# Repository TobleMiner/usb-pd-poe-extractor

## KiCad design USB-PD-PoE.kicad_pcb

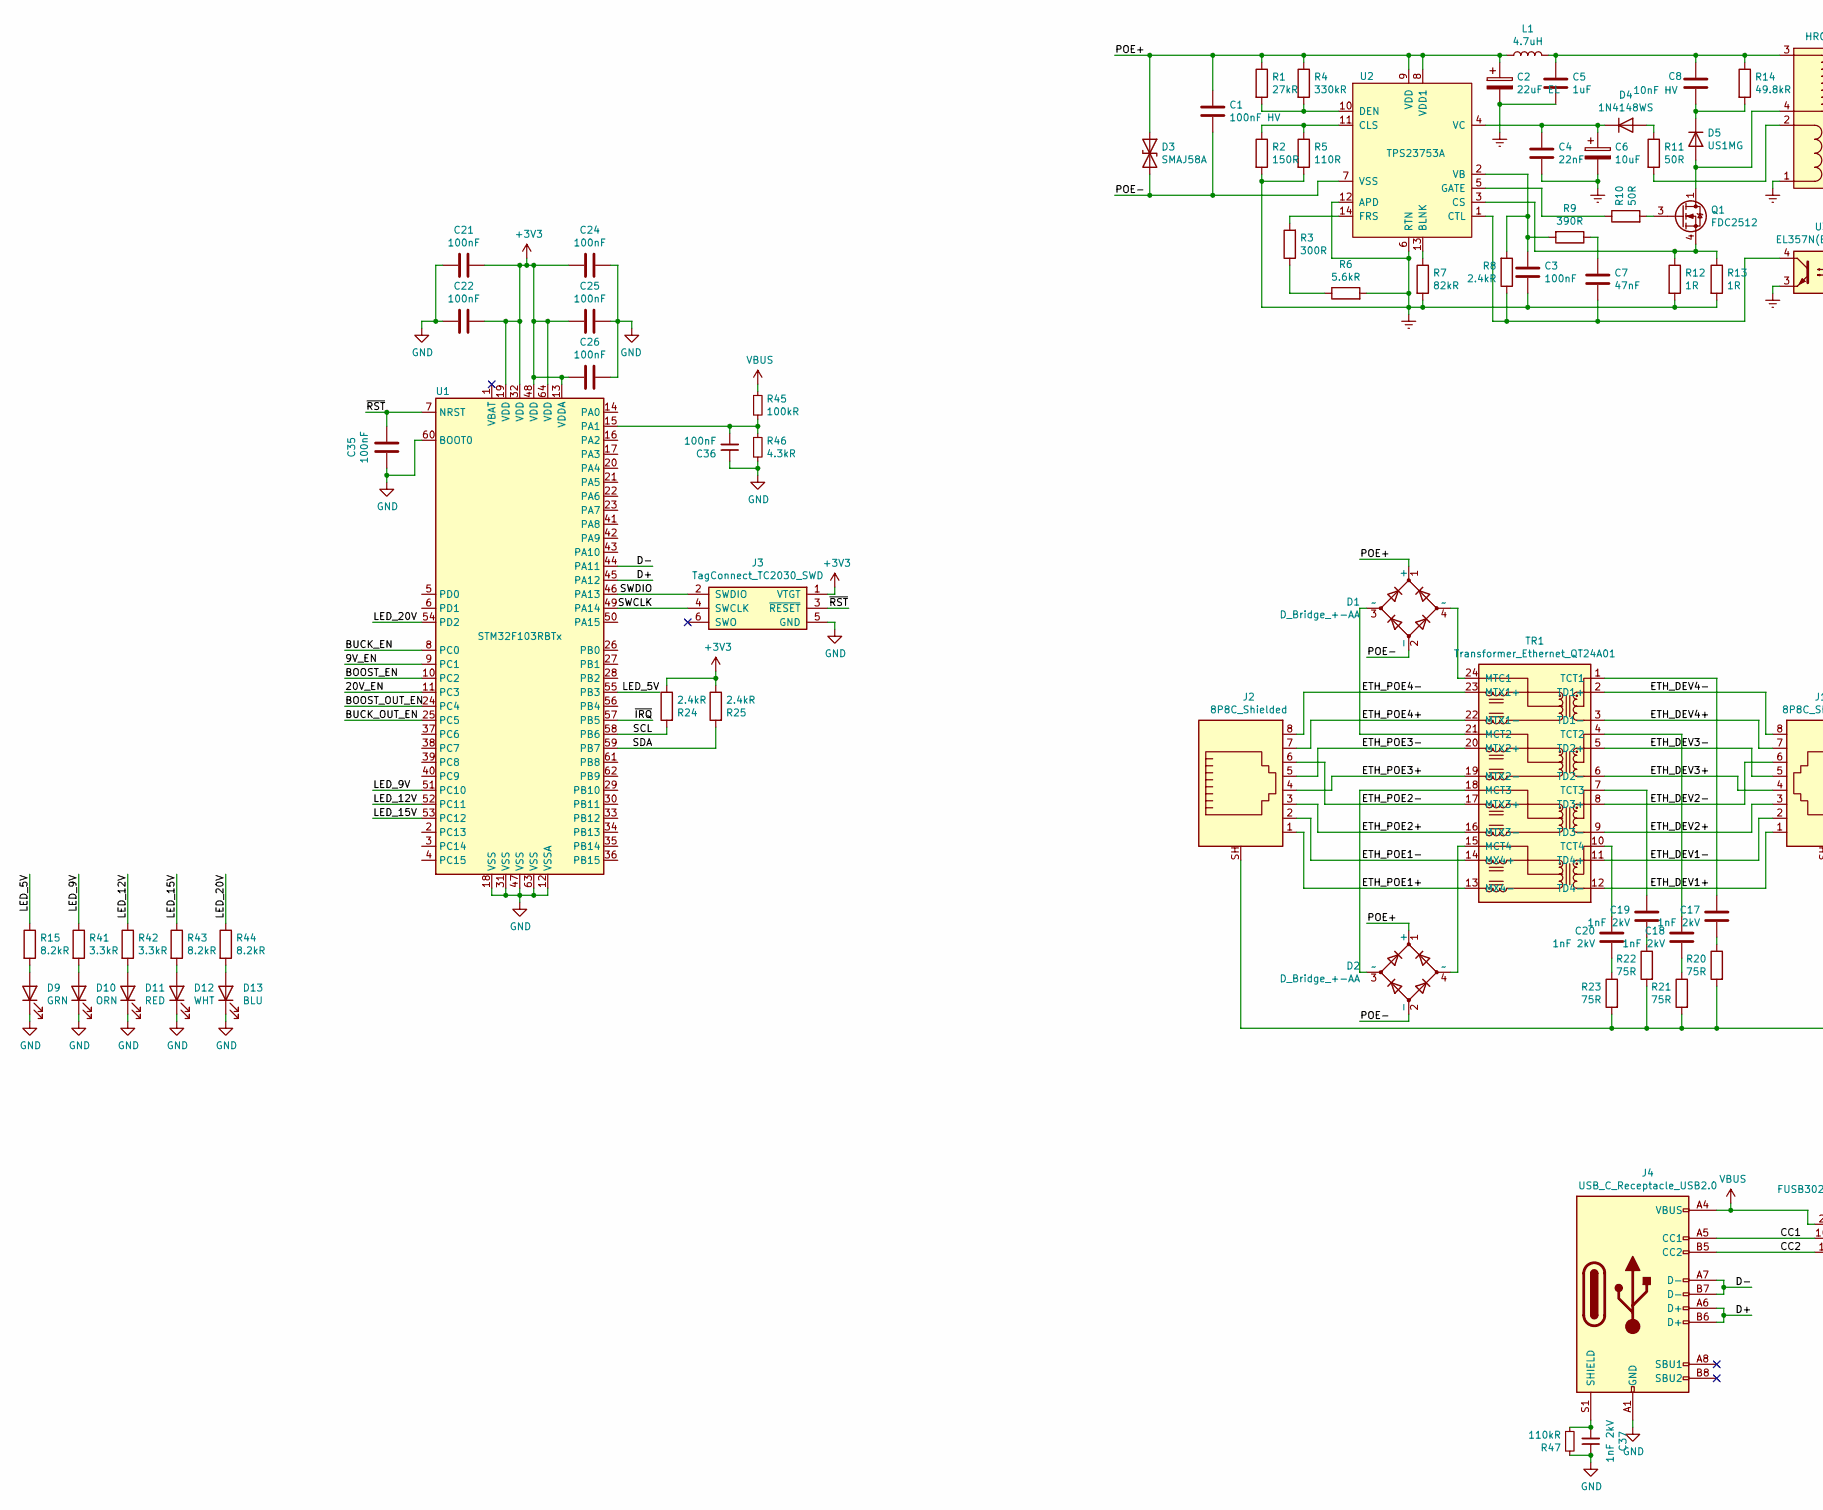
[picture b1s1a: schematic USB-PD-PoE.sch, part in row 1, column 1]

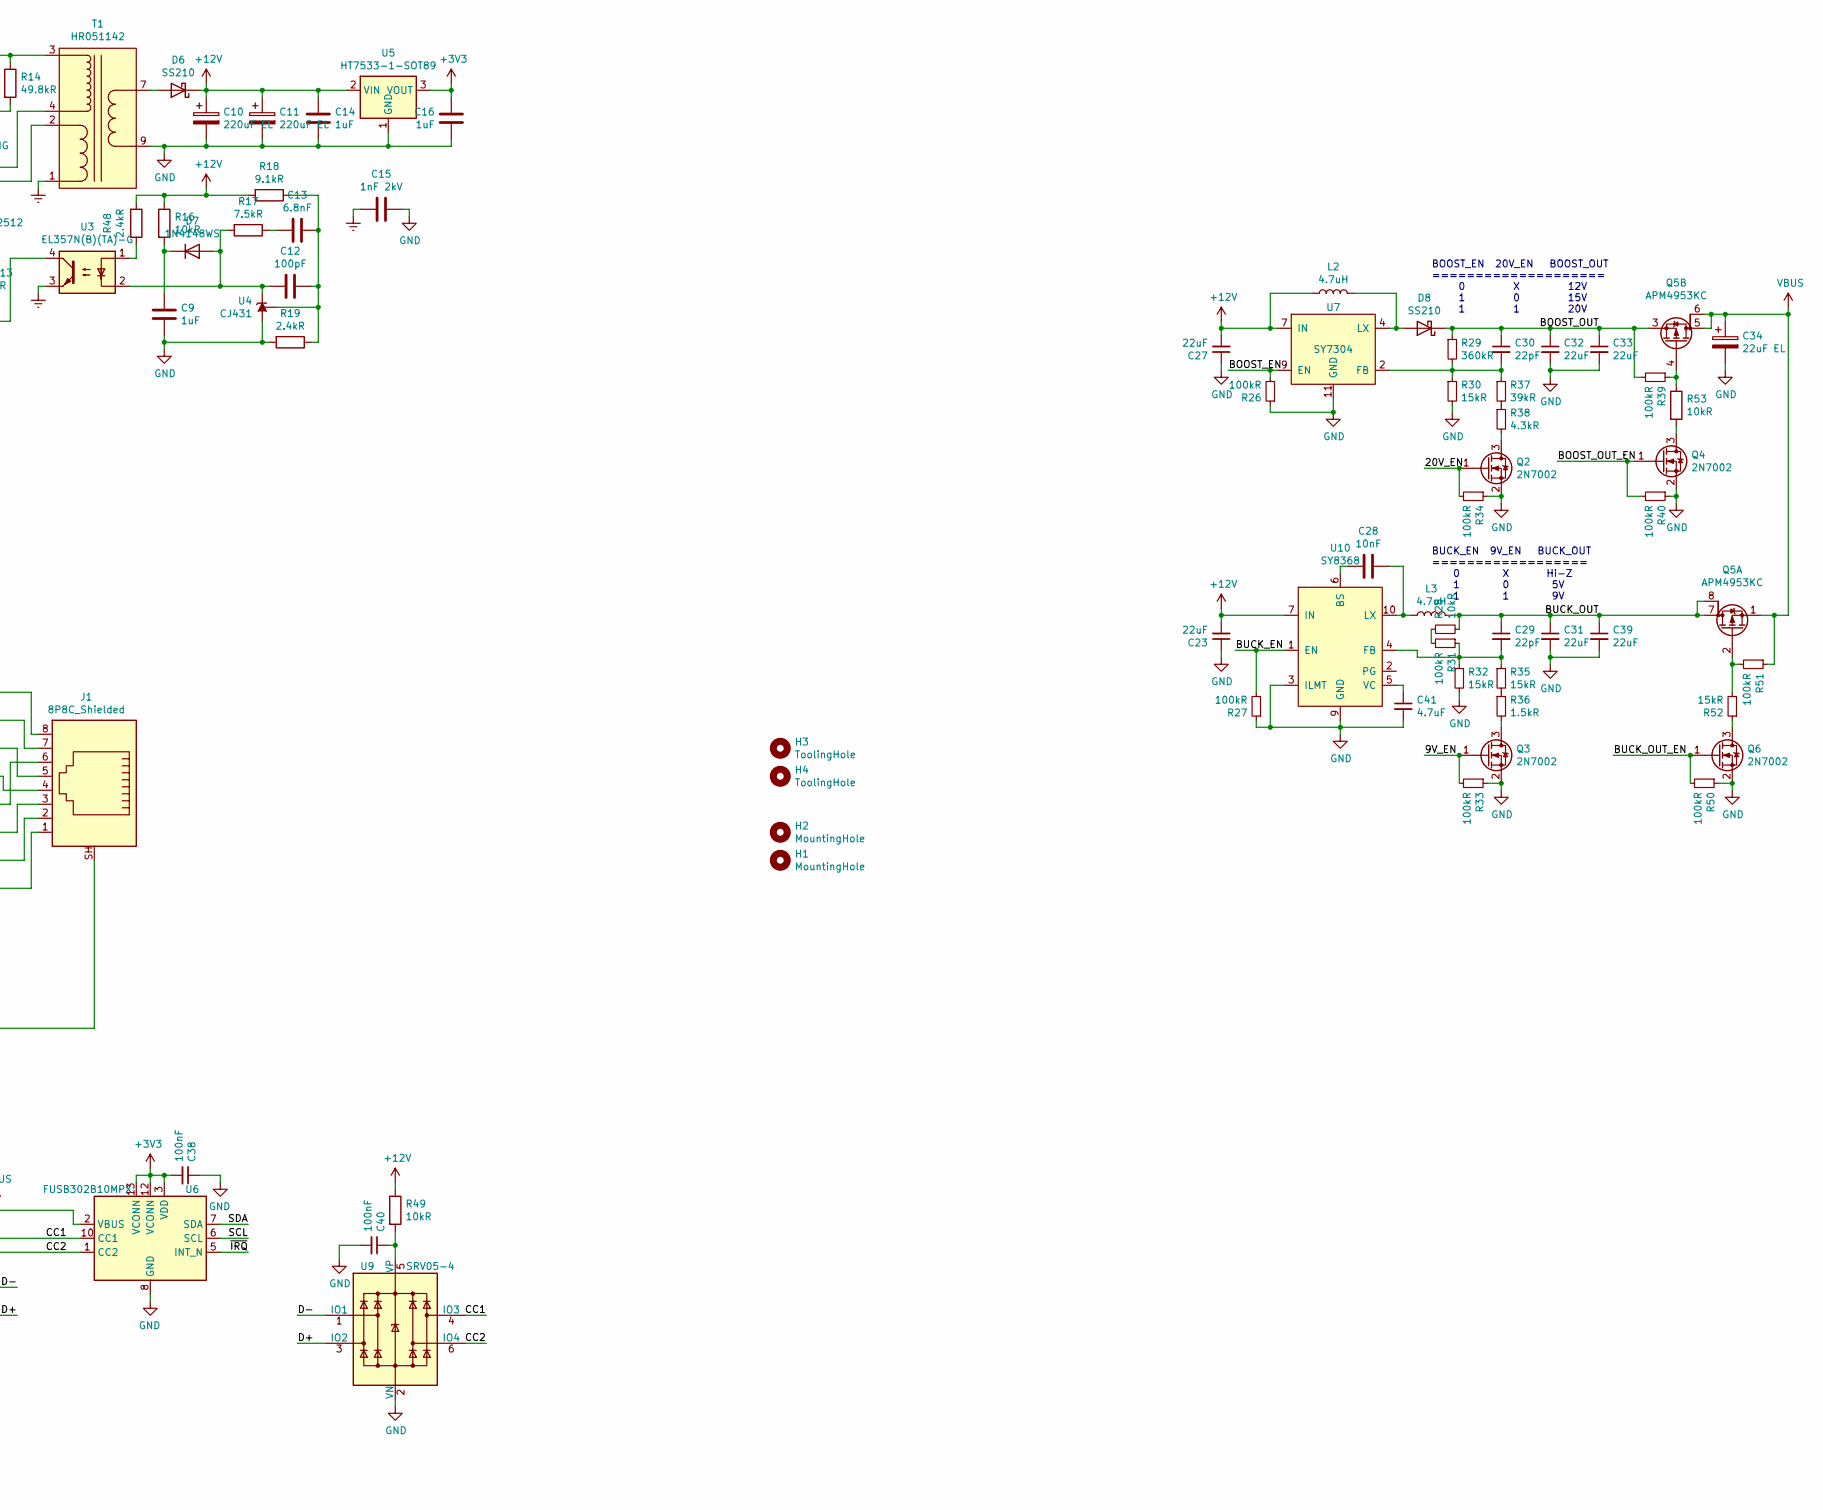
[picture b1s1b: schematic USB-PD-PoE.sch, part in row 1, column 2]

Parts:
C1: 100nF HV; C_1206_3216Metric; LCSC C73745
C2, C34: 22uF EL; CP_Elec_6.3x7.7; LCSC C249868
C3, C21, C22, C24, C25, C26, C35, C36, C38, C40: 100nF; C_0402_1005Metric; LCSC C1525
C4: 22nF; C_0402_1005Metric; LCSC C1532
C5: 1uF; C_1206_3216Metric; LCSC C13832
C6: 10uF; CP_EIA-3216-10_Kemet-I; LCSC C7171
C7: 47nF; C_0603_1608Metric; LCSC C1622
C8: 10nF HV; C_0805_2012Metric; LCSC C18741
C9, C14, C16: 1uF; C_0402_1005Metric; LCSC C52923
C10, C11: 220uF EL; CP_Elec_6.3x7.7; LCSC C127327
C12: 100pF; C_0402_1005Metric; LCSC C1546
C13: 6.8nF; C_0402_1005Metric; LCSC C1542
C15, C17, C18, C19, C20, C37: 1nF 2kV; C_1206_3216Metric; LCSC C328909
C23, C27, C31, C32, C33, C39: 22uF; C_0805_2012Metric; LCSC C45783
C28: 10nF; C_0402_1005Metric; LCSC C15195
C29, C30: 22pF; C_0402_1005Metric; LCSC C1555
C41: 4.7uF; C_0402_1005Metric; LCSC C23733
D1, D2: D_Bridge_+-AA; TO-269AA; LCSC C2488
D3: SMAJ58A; D_SMA; LCSC C115922
D4, D7: 1N4148WS; D_SOD-323F; LCSC C2128
D5: US1MG; D_SMA; LCSC C412437
D6, D8: SS210; D_SMA; LCSC C14996
D9: GRN; LED_0603_1608Metric; LCSC C72043
D10: ORN; LED_0603_1608Metric; LCSC C72038
D11: RED; LED_0603_1608Metric; LCSC C2286
D12: WHT; LED_0603_1608Metric; LCSC C2290
D13: BLU; LED_0603_1608Metric; LCSC C72041
H1: MountingHole; MountingHole_3.2mm_M3
H2: MountingHole; MountingHole_3.2mm_M3_Pad_Via
H3, H4: ToolingHole; ToolingHole_JLCSMT
J1, J2: 8P8C_Shielded; Connector_8P8C_R-RJ45R08P-C000; LCSC C386757
J3: TagConnect_TC2030_SWD; Tag-Connect_TC2030-IDC-NL_2x03_P1.27mm_Vertical
J4: USB_C_Receptacle_USB2.0; USB_C_Receptacle_Palconn_UTC16-G; LCSC C165948
L1, L2, L3: 4.7uH; L_Bourns-SRN6028; LCSC C32684
Q1: FDC2512; SuperSOT-6; LCSC C154516
Q2, Q3, Q4, Q6: 2N7002; SOT-23; LCSC C8545
Q5: APM4953KC; SO-8_3.9x4.9mm_P1.27mm; LCSC C20897
R1: 27kR; R_0402_1005Metric; LCSC C25771
R2: 150R; R_0603_1608Metric; LCSC C22808
R3: 300R; R_0402_1005Metric; LCSC C25102
R4: 330kR; R_0402_1005Metric; LCSC C25778
R5: 110R; R_0603_1608Metric; LCSC C22781
R6: 5.6kR; R_0603_1608Metric; LCSC C25908
R7: 82kR; R_0603_1608Metric; LCSC C23254
R8, R19, R24, R25, R48: 2.4kR; R_0402_1005Metric; LCSC C25882
R9: 390R; R_0603_1608Metric; LCSC C23151
R10, R11: 50R; R_0603_1608Metric; LCSC C23185
R12, R13: 1R; R_0603_1608Metric; LCSC C22936
R14: 49.8kR; R_0603_1608Metric; LCSC C23184
R15, R43, R44: 8.2kR; R_0402_1005Metric; LCSC C25924
R16, R28, R49, R53: 10kR; R_0402_1005Metric; LCSC C25744
R17: 7.5kR; R_0402_1005Metric; LCSC C25918
R18: 9.1kR; R_0603_1608Metric; LCSC C23260
R20, R21, R22, R23: 75R; R_0402_1005Metric; LCSC C25133
R26, R27, R31, R33, R34, R39, R40, R45, R50, R51: 100kR; R_0402_1005Metric; LCSC C25741
R29: 360kR; R_0603_1608Metric; LCSC C23146
R30, R32, R35, R52: 15kR; R_0402_1005Metric; LCSC C25756
R36: 1.5kR; R_0402_1005Metric; LCSC C25867
R37: 39kR; R_0402_1005Metric; LCSC C25783
R38, R46: 4.3kR; R_0603_1608Metric; LCSC C23159
R41, R42: 3.3kR; R_0402_1005Metric; LCSC C25890
R47: 110kR; R_0603_1608Metric; LCSC C25805
T1: HR051142; LCSC C55680
TR1: Transformer_Ethernet_QT24A01; Transformer_Ethernet_TNK_QT24A01; LCSC C216359
U1: STM32F103RBTx; LQFP-64_10x10mm_P0.5mm; LCSC C46034
U2: TPS23753A; TSSOP-14_4.4x5mm_P0.65mm; LCSC C92115
U3: EL357N(B)(TA)-G; SOP-4_3.8x4.1mm_P2.54mm; LCSC C6649
U4: CJ431; SOT-23; LCSC C3113
U5: HT7533-1-SOT89; SOT-89-3; LCSC C14289
U6: FUSB302B10MPX; WQFN-14-1EP_2.5x2.5mm_P0.5mm_EP1.45x1.45mm; LCSC C132291
U7: SY7304; DFN-10-1EP_3x3mm_P0.5mm_EP1.55x2.48mm; LCSC C178252
U9: SRV05-4; SOT-23-6; LCSC C85364
U10: SY8368; QFN_3x3-10_SY8368; LCSC C125897

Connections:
+3V3: C16.1, C21.1, C22.1, C24.2, C25.2, C26.2, C38.2, J3.1 (VTGT), R24.1, R25.1, U1.13 (VDDA), U1.19 (VDD), U1.32 (VDD), U1.48 (VDD), U1.64 (VDD), U5.3 (VOUT), U6.3 (VDD), U6.4 (VDD), U6.12 (VCONN), U6.13 (VCONN)
+12V: C10.1, C11.1, C14.1, C23.2, C27.2, D6.1 (K), L2.1, R16.1, R18.2, R48.1, R49.1, U5.2 (VIN), U7.7 (IN), U10.7 (IN), U10.8 (IN)
/9V_EN: Q3.1 (G), R33.2, U1.9 (PC1)
/20V_EN: Q2.1 (G), R34.2, U1.11 (PC3)
/BOOST_EN: R26.2, U1.10 (PC2), U7.9 (EN)
/BOOST_OUT: C30.1, C32.1, C33.1, D8.1 (K), Q5.3 (S), R29.1, R39.2
/BOOST_OUT_EN: Q4.1 (G), R40.2, U1.24 (PC4)
/BUCK_EN: R27.2, U1.8 (PC0), U10.1 (EN)
/BUCK_OUT: C29.1, C31.1, C39.1, L3.2, Q5.7 (D), Q5.8 (G), R28.2
/BUCK_OUT_EN: Q6.1 (G), R50.2, U1.25 (PC5)
/CC1: J4.A5 (CC1), U6.10 (CC1), U6.11 (CC1), U9.4 (IO3)
/CC2: J4.B5 (CC2), U6.1 (CC2), U6.14 (CC2), U9.6 (IO4)
/D+: J4.A6 (D+), J4.B6 (D+), U1.45 (PA12), U9.3 (IO2)
/D-: J4.A7 (D-), J4.B7 (D-), U1.44 (PA11), U9.1 (IO1)
/ETH_DEV1+: J1.1, TR1.12 (TD4-)
/ETH_DEV1-: J1.2, TR1.11 (TD4+)
/ETH_DEV2+: J1.3, TR1.9 (TD3-)
/ETH_DEV2-: J1.6, TR1.8 (TD3+)
/ETH_DEV3+: J1.4, TR1.6 (TD2-)
/ETH_DEV3-: J1.5, TR1.5 (TD2+)
/ETH_DEV4+: J1.7, TR1.3 (TD1-)
/ETH_DEV4-: J1.8, TR1.2 (TD1+)
/ETH_POE1+: J2.1, TR1.13 (MX4-)
/ETH_POE1-: J2.2, TR1.14 (MX4+)
/ETH_POE2+: J2.3, TR1.16 (MTX3-)
/ETH_POE2-: J2.6, TR1.17 (MTX3+)
/ETH_POE3+: J2.4, TR1.19 (MTX2-)
/ETH_POE3-: J2.5, TR1.20 (MTX2+)
/ETH_POE4+: J2.7, TR1.22 (MTX1-)
/ETH_POE4-: J2.8, TR1.23 (MTX1+)
/LED_5V: R15.1, U1.55 (PB3)
/LED_9V: R41.1, U1.51 (PC10)
/LED_12V: R42.1, U1.52 (PC11)
/LED_15V: R43.1, U1.53 (PC12)
/LED_20V: R44.1, U1.54 (PD2)
/POE+: C1.1, C2.1, D1.1 (+), D2.1 (+), D3.1 (A1), L1.1, R1.1, R4.1, U2.8 (VDD1), U2.9 (VDD)
/POE-: C1.2, D1.2 (-), D2.2 (-), D3.2 (A2), U2.7 (VSS)
/SCL: R24.2, U1.58 (PB6), U6.6 (SCL)
/SDA: R25.2, U1.59 (PB7), U6.7 (SDA)
/SWCLK: J3.4 (SWCLK), U1.49 (PA14)
/SWDIO: J3.2 (SWDIO), U1.46 (PA13)
/~IRQ: U1.57 (PB5), U6.5 (INT_N)
/~RST: C35.1, J3.3 (~RESET), U1.7 (NRST)
Earth: C2.2, C3.2, C4.2, C5.2, C6.2, C15.2, R2.2, R5.2, R6.2, R7.2, R12.2, R13.2, T1.1, U2.6 (RTN), U2.12 (APD), U3.3
GND: C9.2, C10.2, C11.2, C14.2, C15.1, C16.2, C21.2, C22.2, C23.1, C24.1, C25.1, C26.1, C27.1, C31.2, C32.2, C33.2, C34.2, C35.2, C36.1, C37.1, C38.1, C39.2, C40.2, C41.2, D9.1 (K), D10.1 (K), D11.1 (K), D12.1 (K), D13.1 (K), J3.5 (GND), J4.A1 (GND), J4.A12 (GND), J4.B1 (GND), J4.B12 (GND), Q2.2 (S), Q3.2 (S), Q4.2 (S), Q6.2 (S), R19.2, R26.1, R27.1, R30.2, R32.2, R33.1, R34.1, R40.1, R46.2, R47.2, R50.1, T1.9, T1.10, U1.12 (VSSA), U1.18 (VSS), U1.31 (VSS), U1.47 (VSS), U1.60 (BOOT0), U1.63 (VSS), U4.3 (A), U5.1 (GND), U6.8 (GND), U6.9 (GND), U6.15 (GND), U7.11 (GND), U9.2 (VN), U10.3 (ILMT), U10.9 (GND)
unnamed: C3.1, R8.2, R9.2, U2.2 (VB)
unnamed: C4.1, C6.1, D4.1 (K), U2.4 (VC)
unnamed: C5.1, C8.1, L1.2, R14.1, T1.3
unnamed: C7.1, R9.1
unnamed: C7.2, R8.1, U2.1 (CTL), U3.4
unnamed: C8.2, D5.1 (K), R14.2
unnamed: C9.1, D7.1 (K), R16.2
unnamed: C12.1, C13.1, R18.1, R19.1, U4.1 (REF)
unnamed: C12.2, D7.2 (A), R17.2, U3.2, U4.2 (K)
unnamed: C13.2, R17.1
unnamed: C17.1, R20.1
unnamed: C17.2, TR1.1 (TCT1)
unnamed: C18.1, R21.1
unnamed: C18.2, TR1.4 (TCT2)
unnamed: C19.1, R22.1
unnamed: C19.2, TR1.7 (TCT3)
unnamed: C20.1, R23.1
unnamed: C20.2, TR1.10 (TCT4)
unnamed: C28.1, L3.1, U10.10 (LX)
unnamed: C28.2, U10.6 (BS)
unnamed: C29.2, R31.1, R32.1, R35.1, U10.4 (FB)
unnamed: C30.2, R29.2, R30.1, R37.1, U7.2 (FB)
unnamed: C36.2, R45.2, R46.1, U1.15 (PA1)
unnamed: C37.2, J4.S1 (SHIELD), R47.1
unnamed: C40.1, R49.2, U9.5 (VP)
unnamed: C41.1, U10.5 (VC)
unnamed: D1.3 (~~), TR1.21 (MCT2)
unnamed: D1.4 (~~), TR1.24 (MTC1)
unnamed: D2.3 (~~), TR1.18 (MCT3)
unnamed: D2.4 (~~), TR1.15 (MCT4)
unnamed: D4.2 (A), R11.1
unnamed: D5.2 (A), Q1.1 (D), Q1.2 (D), Q1.5 (D), Q1.6 (D), T1.4
unnamed: D6.2 (A), T1.7, T1.8
unnamed: D8.2 (A), L2.2, U7.4 (LX), U7.5 (LX)
unnamed: D9.2 (A), R15.2
unnamed: D10.2 (A), R41.2
unnamed: D11.2 (A), R42.2
unnamed: D12.2 (A), R43.2
unnamed: D13.2 (A), R44.2
unnamed: J1.SH, J2.SH, R20.2, R21.2, R22.2, R23.2
unnamed: Q1.3 (G), R10.2
unnamed: Q1.4 (S), R12.1, R13.1, U2.3 (CS)
unnamed: Q2.3 (D), R38.2
unnamed: Q3.3 (D), R36.2
unnamed: Q4.3 (D), R53.2
unnamed: Q5.2 (G), R51.2, R52.2
unnamed: Q5.4 (G), R39.1, R53.1
unnamed: Q6.3 (D), R52.1
unnamed: R1.2, R4.2, U2.10 (DEN)
unnamed: R2.1, R5.1, U2.11 (CLS)
unnamed: R3.1, R6.1
unnamed: R3.2, U2.14 (FRS)
unnamed: R7.1, U2.13 (BLNK)
unnamed: R10.1, U2.5 (GATE)
unnamed: R11.2, T1.2
unnamed: R28.1, R31.2
unnamed: R35.2, R36.1
unnamed: R37.2, R38.1
unnamed: R48.2, U3.1
VBUS: C34.1, J4.A4 (VBUS), J4.A9 (VBUS), J4.B4 (VBUS), J4.B9 (VBUS), Q5.1 (S), Q5.5 (D), Q5.6 (G), R45.1, R51.1, U6.2 (VBUS)

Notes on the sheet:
BOOST_EN 20V_EN BOOST_OUT ==================== 0 X 12V 1 0 15V 1 1 20V
BUCK_EN 9V_EN BUCK_OUT ================== 0 X Hi-Z 1 0 5V 1 1 9V

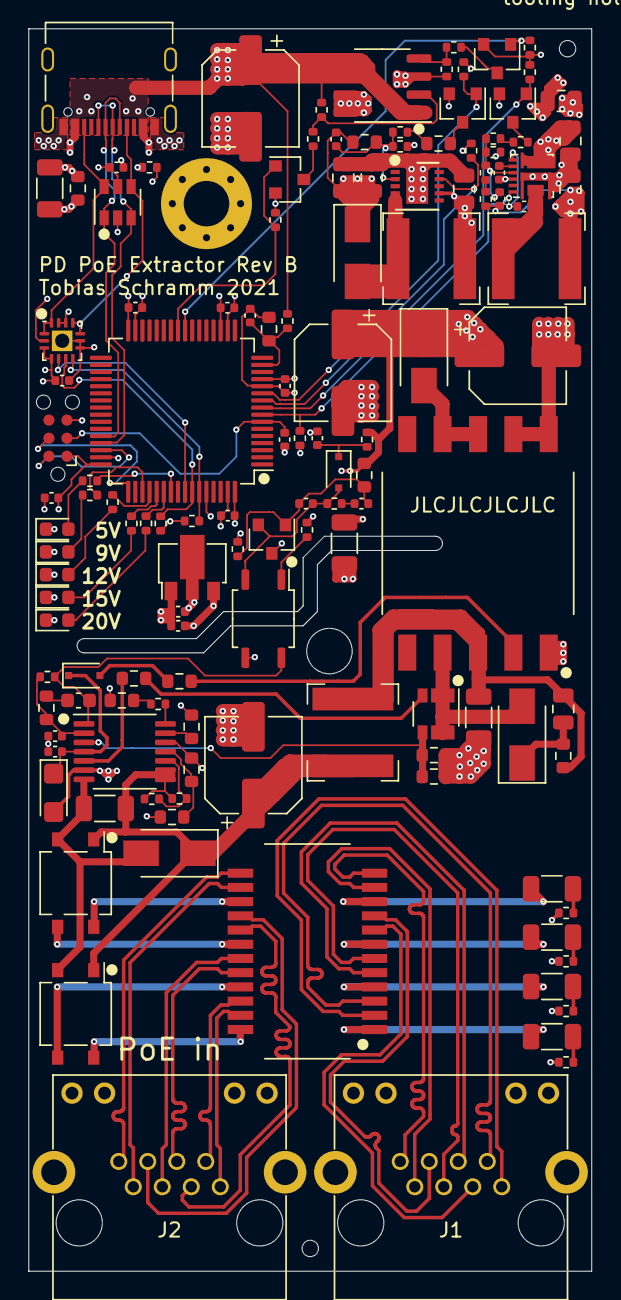
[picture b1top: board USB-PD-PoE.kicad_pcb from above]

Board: 4 copper layers, 39.6 x 87.4 mm, 135 parts (0 on the bottom side), 105 nets.

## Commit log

2021-03-08 Hide footprint references
2021-03-08 Add tooling holes
2021-03-08 Fix PA <-> PB mixup
2021-03-08 Fix GND copper zone clearance issues
2021-03-08 Center silkscreen designator alignment
2021-03-08 Remove GND fill below L2 and L3
2021-03-08 Improve VBUS current carrying capability
2021-03-08 Protect screw holes from layer shorts
2021-03-08 Add USB/CC protection diode
2021-03-08 Remove +12V stub
2021-03-08 Hide USB TVS silkscreen reference
2021-03-08 Add pin 1 indicator to USB TVS
2021-04-10 Fix reversed CJ431 pinout
2021-04-10 Add more bulk capacitance on flyback output
2021-04-10 Add buck converter power gating
2021-04-10 Move 5V LED away from JTAG pins
2021-04-11 Fix ethernet transformer footprint
2021-04-19 Add Silergy SY8368 synchronous step-down regulator
2021-04-19 Include SY8368 to library table
2021-04-19 Add RJ45R08P-C000 variant C
2021-04-19 Optimize design for manufacturing
    Replace components not available at JLC anymore.
